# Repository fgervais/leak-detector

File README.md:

# TinyPICO/ESP32 Leak Detector

Detect leaks, trigger an alarm and send a notification to your phone.

It can be used to save your wood flooring for example as wiping the water off
a couple minutes sooner can make a difference.

## Complete System

## Detection Electrode

To detect a leak, the idea is that water need to bridge the 2 screw terminal
leads.

On my end what I'm doing for this project is using copper tape traces that run
close to each other. Basically the same technique used by some types of user
buttons but bigger.

Those copper traces are on a sheet of paper allowing even a single drop of water
to have quite a wide coverage. This way really little water is required to get
a detection even in the worse case.

## Battery Power

With the first revision of this project, I went with the micropython version
shipped with the TinyPICO and a single 18650 cell. I was aiming to get a
3 years run between recharge but I only got 37 weeks.

Further investigation showed that the majority of the power was used by the
touch detection as the default touch sensor parameters are quite aggressive.

To fix this, I had to expose more of the touch sensor API as shown here:
https://github.com/micropython/micropython/pull/6408. With this I was able to
change the touch sensor polling rate from 37 Hz to about 2 Hz. I also reduced
the time it stays on, looking for a touch.

With these changes in place, the limiting factor for the battery life seemed to
be the self-discharge of the li-ion cell. To mitigate that I changed the 18650
cell by 3 AA Energizer® Ultimate Lithium batteries. These are advertised to
have a really low self discharge and I'm hoping they will perform as so.

## Blynk

The detector gets controlled by a [Blynk](https://blynk.io/) app.

In the Blynk app you see a beacon that is sent by the device every week so you
know the device is still alive. The beacon is dual purpose as the data is the
battery voltage capped to 3.7v.

In the screenshot you can see the li-ion battery discharging to full to about
dead in 37 weeks.

Note that this was before changing the battery type and [optimizing](https://github.com/fgervais/leak-detector/commit/07dddd6354a1dfdce8fd6b8dc646baeb9ef110fd)
the touch sensor power consumption. The battery should last much longer now.

Blynk Project | Blynk Project Clone QR
:-------------------------:|:-------------------------:
  |  

The QR code should give you a complete copy of my project if scanned in the
Blynk app.

# Hardware

The board (rev1) and the BOM are accessible here:

- https://oshpark.com/shared_projects/Uk5klm7L
- https://www.digikey.ca/short/z0c01q

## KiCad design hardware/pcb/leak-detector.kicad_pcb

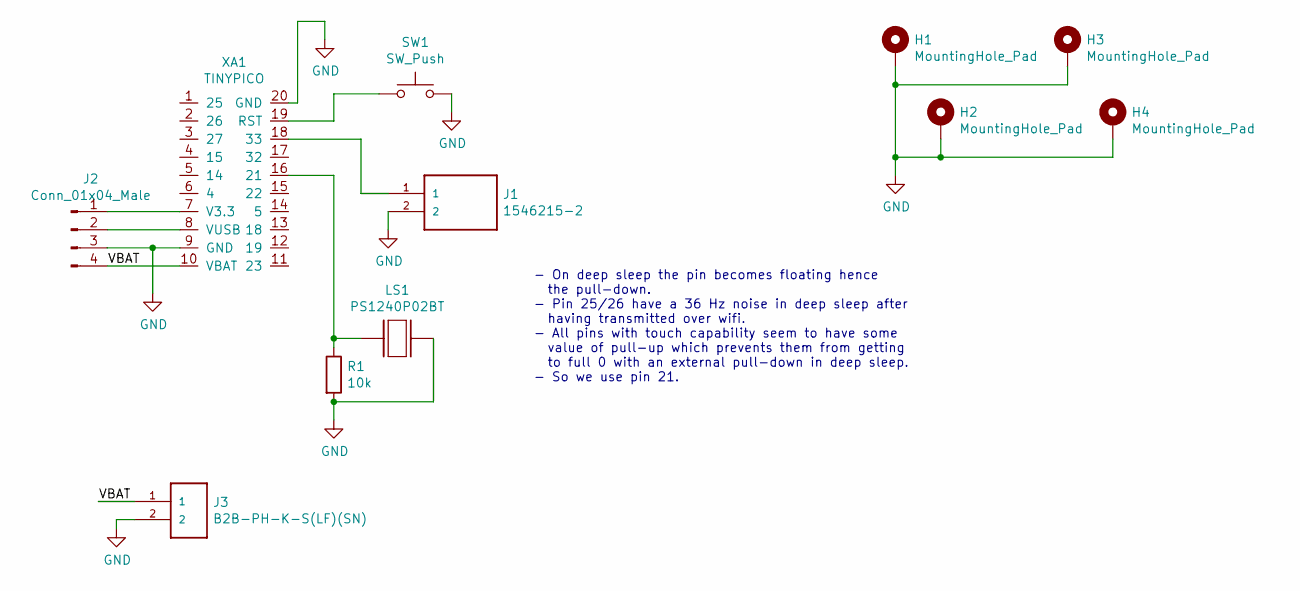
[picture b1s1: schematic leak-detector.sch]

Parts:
H1, H2, H3, H4: MountingHole_Pad; MountingHole_2.7mm_M2.5_ISO7380_Pad
J1: 1546215-2; TE_1546215-2
J2: Conn_01x04_Male; PinHeader_1x04_P2.54mm_Vertical
J3: B2B-PH-K-S(LF)(SN); JST_B2B-PH-K-S(LF)(SN)
LS1: PS1240P02BT; XDCR_PS1240P02BT
R1: 10k; R_0603_1608Metric_Pad1.05x0.95mm_HandSolder
SW1: SW_Push; SW_SPST_TL3342
XA1: TINYPICO

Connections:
/VBAT: J2.4, J3.1, XA1.10 (VBAT)
GND: H1.1, H2.1, H3.1, H4.1, J1.2, J2.3, J3.2, LS1.2, R1.2, SW1.2, XA1.9 (GND), XA1.20 (GND)
unnamed: J1.1, XA1.18 (33)
unnamed: J2.1, XA1.7 (V3.3)
unnamed: J2.2, XA1.8 (VUSB)
unnamed: LS1.1, R1.1, XA1.16 (21)
unnamed: SW1.1, XA1.19 (RST)

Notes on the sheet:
- On deep sleep the pin becomes floating hence the pull-down. - Pin 25/26 have a 36 Hz noise in deep sleep after having transmitted over wifi. - All pins with touch capability seem to have some value of pull-up which prevents them from getting to full 0 with an external pull-down in deep sleep. - S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

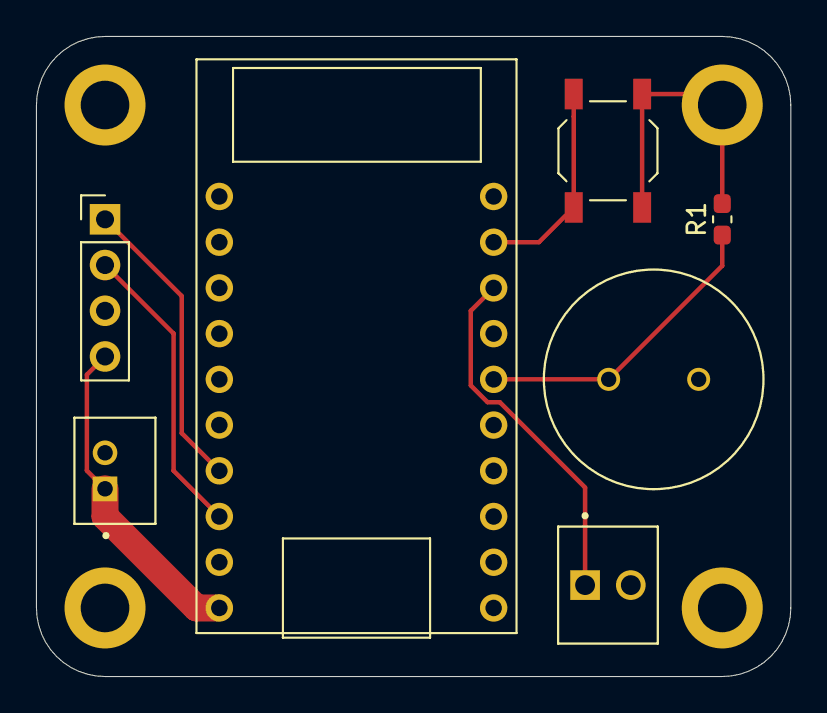
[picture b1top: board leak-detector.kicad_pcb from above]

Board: 2 copper layers, 41.9 x 35.6 mm, 11 parts (0 on the bottom side), 7 nets.

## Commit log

2019-10-14 A bit of everything
2019-10-30 Tested version
2019-11-02 Report a leak when detected
2019-11-09 Long term test (report every hour)
2019-11-09 Print a smiley face on detection
2019-11-12 Remove smiley face
2019-11-12 Add show_leak_cap_value()
2019-11-12 When charging wake up every 5 minutes
2019-11-12 Do not call run() on disconnect()
2019-11-12 Add the charging led
2019-11-12 Show leak capacitance on boot
2019-11-14 Add buzzer support
2019-11-14 Ring alarm for 1 minute, sleep for 3 minutes
2019-11-14 Report the leak once
2019-11-14 Ring alarm for specified seconds
2019-11-14 Fix rtc.memory access
2019-11-14 Give connection management to Device
2019-11-14 Add blynk_notify()
2019-11-14 Move error_reported
2019-11-24 Battery charging workaround
2019-11-24 When charging, wake-up every 30 minutes
2019-11-24 Little beep only on power on
2019-11-25 Only check if battery is charging if there is no leak
2019-11-25 Disconnect wifi before going to sleep
2019-12-01 Sleep for 1 week between beacon pings
2019-12-01 On leak, alarm 60s, sleep forever
2019-12-04 Remove the buggy charge indicator
2020-08-25 Add ampy to the project
2020-08-25 Ignore any secret files
2020-08-31 Use pin 27 for the buzzer
    It seem that this pin doesn't have the 36 Hz noise when in deep sleep.
2020-09-05 Use pin 21 for the buzzer
    The pin 27 seems to have some value of pull-up and so can't be completely
    pulled down in deep sleep resulting in some current loss.
2020-09-05 Reduce the current used by the touch sensor
    Reduced by a factor of 64 (16*4).
2020-09-05 Add a comment about wifi connection
2020-09-05 Display the touchpad value in the app
2020-09-12 Add pcb rev 2
    This version has the JST-PH battery connector.
2020-09-24 Add LICENSE
2020-09-27 Change leak threshold to 10
2020-09-27 Add README
2020-09-27 Fix board image extension
2020-09-27 Change image size
2020-09-27 Add more blynk description
2020-09-27 Change image position
2020-09-27 Remove some newlines
2020-10-09 Add more description to the readme
2020-10-21 Change board picture
2020-11-10 Remove unneeded files
2020-11-10 Add OSHPARK and Digi-Key order links
